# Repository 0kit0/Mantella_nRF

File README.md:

# Mantella_nRF
A small/wearable NFC to BLE bridge.

The project is an adaptation of the LimiTTer project by JoernL and the LBridge code by keencave.

It utilises a nRF52 BLE uC and a CR95HF NFC controller to collect information from an NFC tag and transmit it over BLE to a remote device.

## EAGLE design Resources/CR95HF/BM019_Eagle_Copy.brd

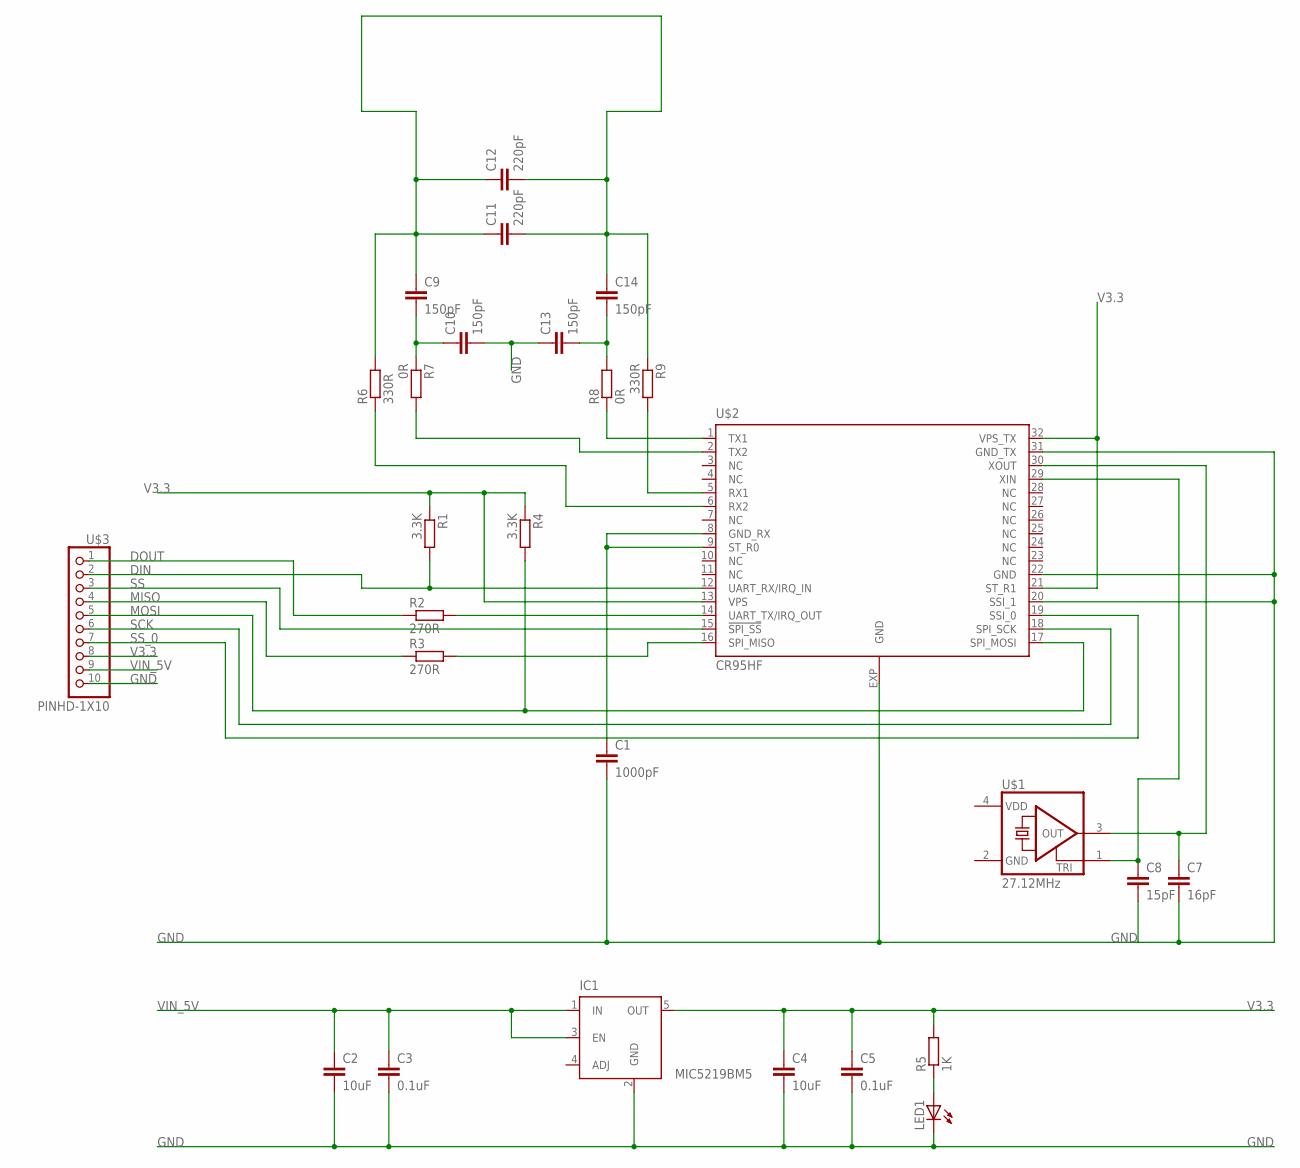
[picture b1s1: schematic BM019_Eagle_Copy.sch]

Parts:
C1: 1000pF; C0603
C2, C4: 10uF; C0603
C3, C5: 0.1uF; C0603
C7: 16pF; C0603
C8: 15pF; C0603
C9, C10, C13, C14: 150pF; C0603
C11, C12: 220pF; C0603
IC1: MIC5219BM5; SOT23-5
LED1: LEDCHIPLED_0603; CHIPLED_0603
R1, R4: 3.3K; R0603
R2, R3: 270R; R0603
R5: 1K; R0603
R6, R9: 330R; R0603
R7, R8: 0R; R0603
U$1: 27.12MHz; ASE
U$2: CR95HF; VFQFPN32
U$3: PINHD-1X10; 1X10-BIG

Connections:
DIN: R1.2, U$2.12 (UART_RX/IRQ_IN), U$3.2
DOUT: R2.1, U$3.1
GND: C1.2, C2.2, C3.2, C4.2, C5.2, C7.2, C8.2, C10.2, C13.1, IC1.2 (GND), LED1.C, U$1.2 (GND), U$2.20 (SSI_1), U$2.22 (GND), U$2.31 (GND_TX), U$2.EXP (GND), U$3.10
MISO: R3.1, U$3.4
MOSI: R4.2, U$2.17 (SPI_MOSI), U$3.5
unnamed: R7.2, U$2.2 (TX2)
unnamed: R3.2, U$2.16 (SPI_MISO)
unnamed: R8.1, U$2.1 (TX1)
unnamed: R9.2, U$2.5 (RX1)
unnamed: R2.2, U$2.14 (UART_TX/IRQ_OUT)
unnamed: LED1.A, R5.1
unnamed: C1.1, U$2.8 (GND_RX), U$2.9 (ST_R0)
unnamed: C9.2, C10.1, R7.1
unnamed: C13.2, C14.2, R8.2
unnamed: C9.1, C11.1, C11.2, C12.1, C12.2, C14.1, R6.2, R9.1
unnamed: C8.1, U$1.1 (TRI), U$2.29 (XIN)
unnamed: C7.1, U$1.3 (OUT), U$2.30 (XOUT)
unnamed: R6.1, U$2.6 (RX2)
NC: U$2.4 (NC), U$2.7 (NC), U$2.10 (NC)
SCK: U$2.18 (SPI_SCK), U$3.6
SS: U$2.15 (!SPI_SS), U$3.3
SS_0: U$2.19 (SSI_0), U$3.7
V3.3: C4.1, C5.1, IC1.5 (OUT), R1.1, R4.1, R5.2, U$2.13 (VPS), U$2.21 (ST_R1), U$2.32 (VPS_TX), U$3.8
VDD: U$1.4 (VDD)
VIN_5V: C2.1, C3.1, IC1.1 (IN), IC1.3 (EN), U$3.9

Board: 2 copper layers, 27 parts (0 on the bottom side), 24 nets, no tracks yet.
